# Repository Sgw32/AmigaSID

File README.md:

# AmigaSID - A2000 version is main

Amiga SID Zorro II card

Use at your own risk!!!

Project forked from: 
http://www.amibay.com/showthread.php?108629-Amiga-SID-player-for-Zorro-slot

Player: http://aminet.net/package/misc/emu/FrodoV2_4

Videos:
https://www.youtube.com/watch?app=desktop&v=QOlyukb5uWo
https://www.youtube.com/watch?v=6BfD3O8DvEo

Project information in "original" folder

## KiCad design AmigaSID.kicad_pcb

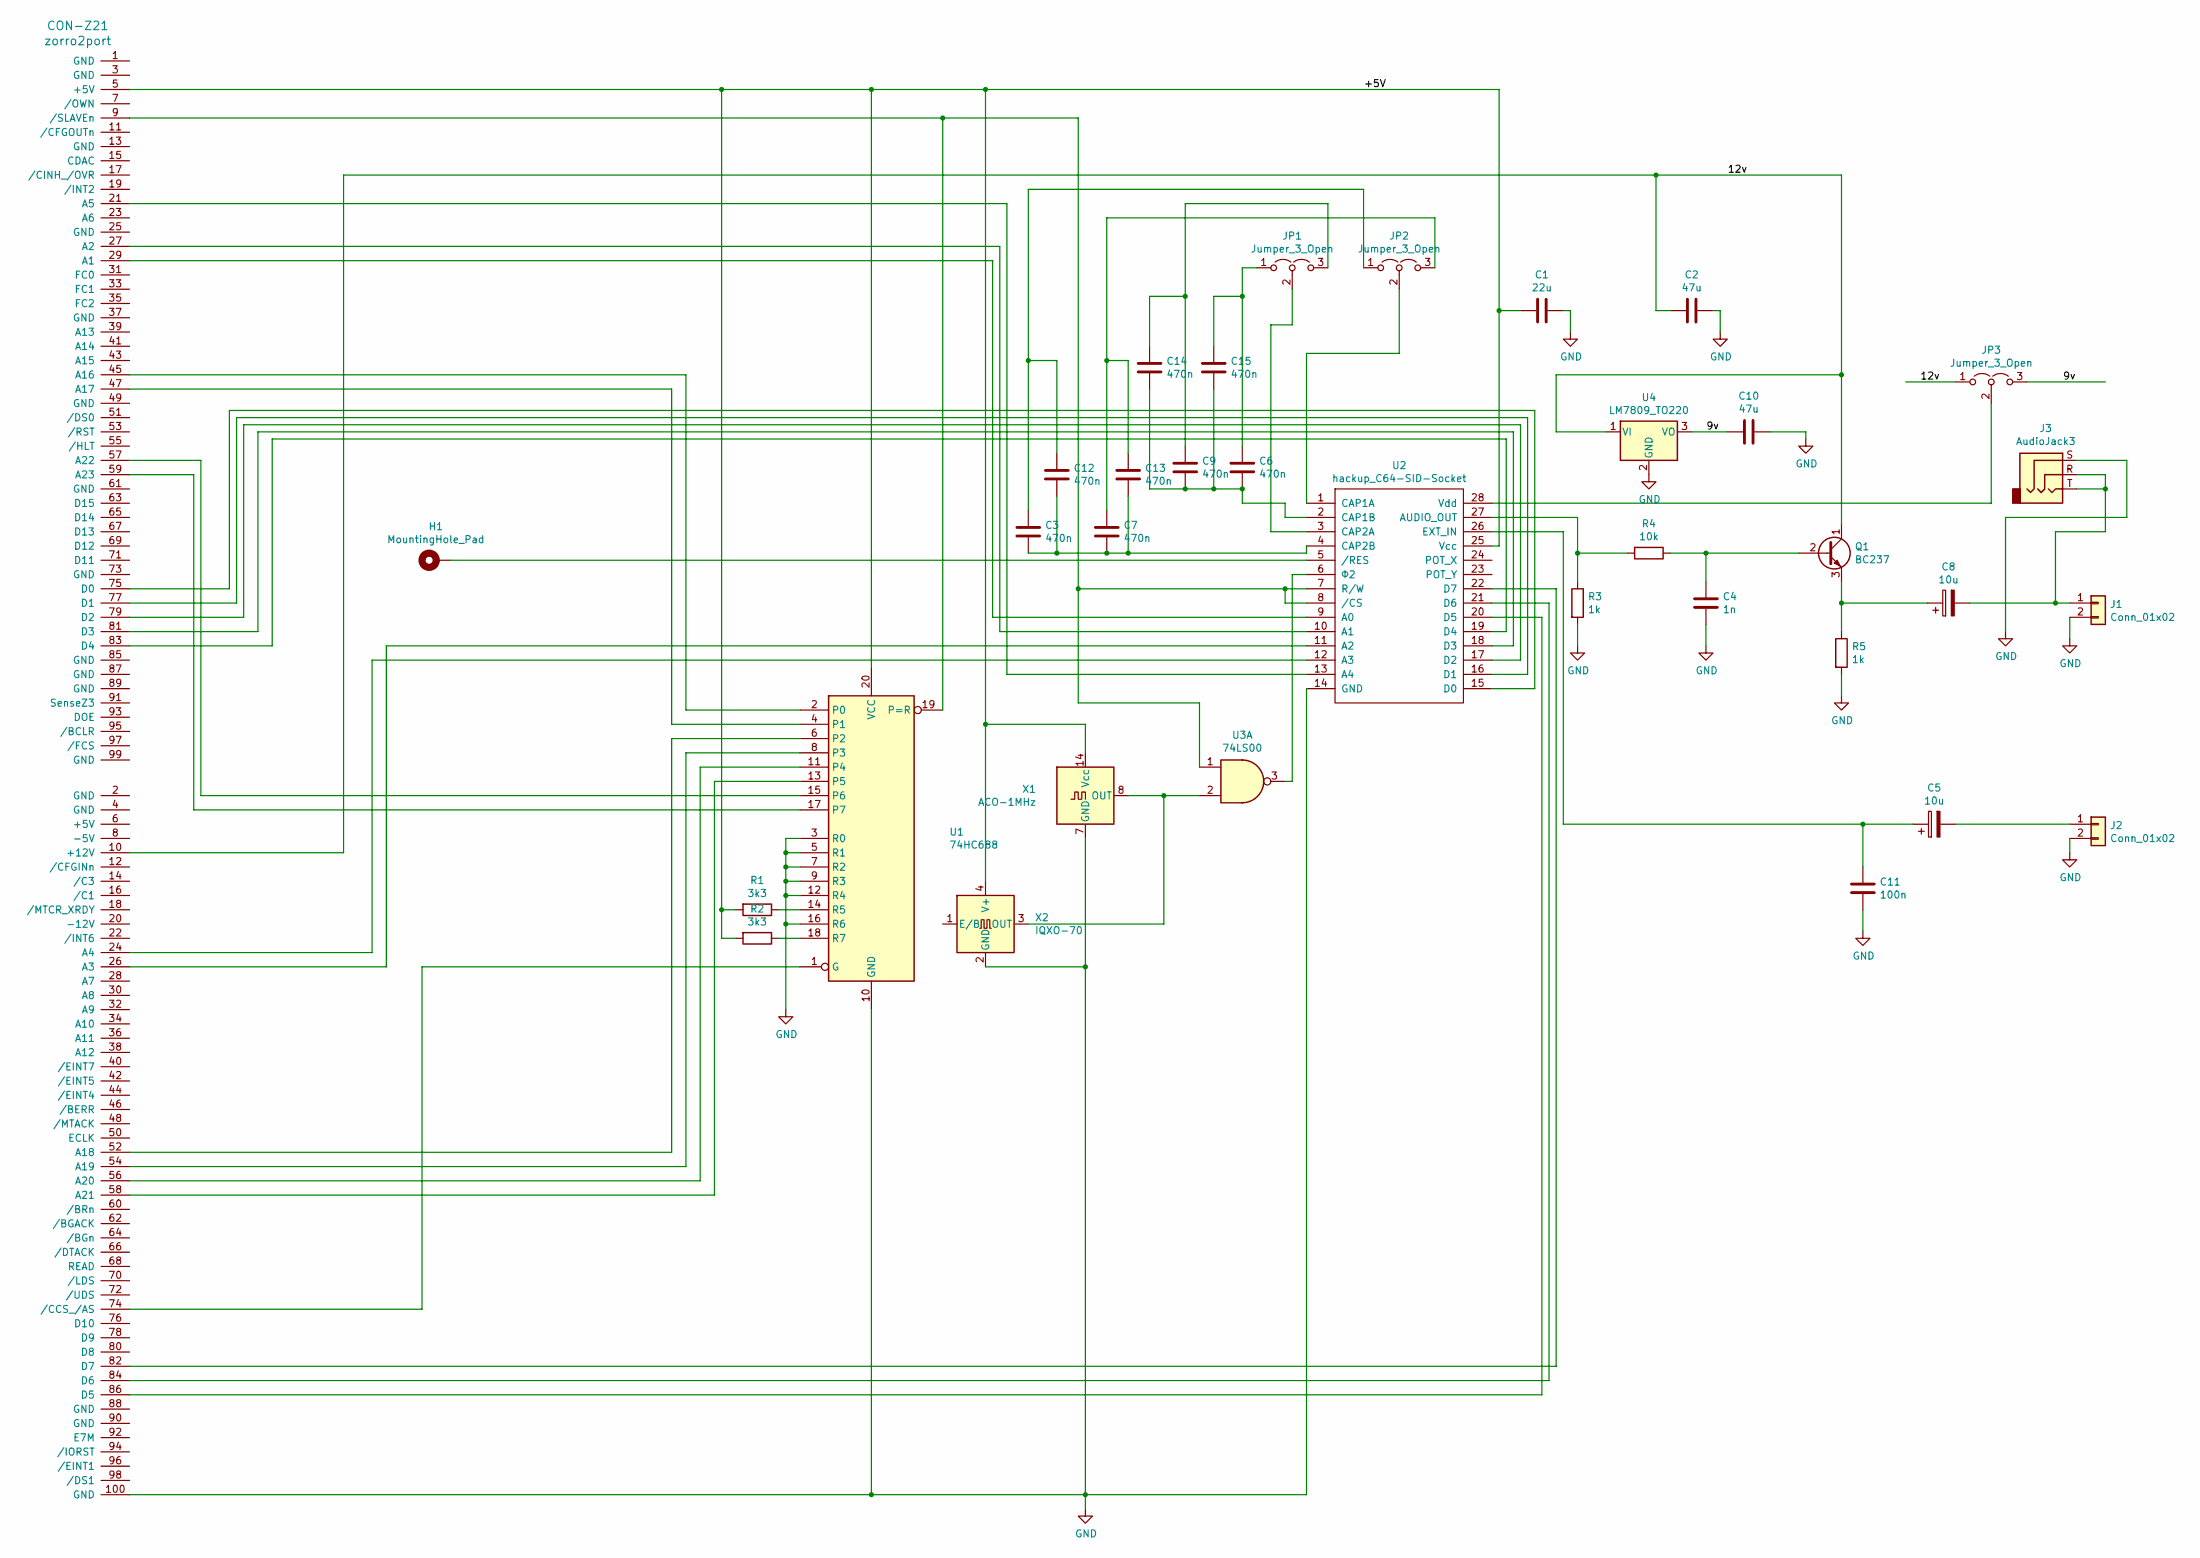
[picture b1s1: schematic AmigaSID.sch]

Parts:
C1: 22u; C_Disc_D4.7mm_W2.5mm_P5.00mm
C2, C10: 47u; C_Disc_D4.7mm_W2.5mm_P5.00mm
C3, C6, C7, C9: 470n; C_Disc_D4.7mm_W2.5mm_P5.00mm
C4: 1n; C_Disc_D4.7mm_W2.5mm_P5.00mm
C5, C8: 10u; CP_Radial_D7.5mm_P2.50mm
C11: 100n; C_Disc_D4.7mm_W2.5mm_P5.00mm
C12, C13, C14, C15: 470n; C_0805_2012Metric
CON-Z21: zorro2port; zorro2card
H1: MountingHole_Pad; Pin_D0.7mm_L6.5mm_W1.8mm_FlatFork
J1, J2: Conn_01x02; TerminalBlock_4Ucon_1x02_P3.50mm_Horizontal
J3: AudioJack3; Jack_3.5mm_CUI_SJ1-3533NG_Horizontal_CircularHoles
JP1, JP2, JP3: Jumper_3_Open; PinHeader_1x03_P2.54mm_Vertical
Q1: BC237; TO-92_Inline
R1, R2: 3k3; R_Axial_DIN0207_L6.3mm_D2.5mm_P10.16mm_Horizontal
R3, R5: 1k; R_Axial_DIN0207_L6.3mm_D2.5mm_P10.16mm_Horizontal
R4: 10k; R_Axial_DIN0207_L6.3mm_D2.5mm_P10.16mm_Horizontal
U1: 74HC688; DIP-20_W7.62mm_Socket_LongPads
U2: hackup_C64-SID-Socket; DIP-28_W15.24mm_Socket_LongPads
U3: 74LS00; DIP-14_W7.62mm_Socket_LongPads
U4: LM7809_TO220; TO-220-3_Vertical
X1: ACO-1MHz; Oscillator_DIP-14
X2: IQXO-70; Oscillator_SMD_IQD_IQXO70-4Pin_7.5x5.0mm

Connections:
/9v: C10.2, JP3.3 (B), U4.3 (VO)
/12v: C2.2, CON-Z21.10 (+12V), JP3.1 (A), Q1.1 (C), U4.1 (VI)
/+5V: C1.2, CON-Z21.5 (+5V), R1.2, R2.2, U1.20 (VCC), U2.25 (Vcc), X1.14 (Vcc), X2.4 (V+)
GND: C1.1, C2.1, C4.2, C10.1, C11.2, CON-Z21.100 (GND), J1.2, J2.2, J3.S, R3.2, R5.2, U1.3 (R0), U1.5 (R1), U1.7 (R2), U1.9 (R3), U1.10 (GND), U1.12 (R4), U1.16 (R6), U2.14 (GND), U4.2 (GND), X1.7 (GND), X2.2 (GND)
unnamed: C4.1, Q1.2 (B), R4.1
unnamed: C5.2, J2.1
unnamed: C8.1, Q1.3 (E), R5.1
unnamed: C8.2, J1.1, J3.R, J3.T
unnamed: C5.1, C11.1, U2.26 (EXT_IN)
unnamed: C3.1, C12.1, JP2.1 (A)
unnamed: C3.2, C7.2, C12.2, C13.2, U2.4 (CAP2B)
unnamed: C7.1, C13.1, JP2.3 (B)
unnamed: C9.1, C14.1, JP1.3 (B)
unnamed: C6.2, C9.2, C14.2, C15.2, U2.2 (CAP1B)
unnamed: C6.1, C15.1, JP1.1 (A)
unnamed: CON-Z21.9 (/SLAVEn), U1.19 (P=R), U2.7 (R/W), U2.8 (/CS), U3.1
unnamed: CON-Z21.21 (A5), U2.13 (A4)
unnamed: CON-Z21.24 (A4), U2.12 (A3)
unnamed: CON-Z21.26 (A3), U2.11 (A2)
unnamed: CON-Z21.27 (A2), U2.10 (A1)
unnamed: CON-Z21.29 (A1), U2.9 (A0)
unnamed: CON-Z21.45 (A16), U1.2 (P0)
unnamed: CON-Z21.47 (A17), U1.4 (P1)
unnamed: CON-Z21.52 (A18), U1.6 (P2)
unnamed: CON-Z21.54 (A19), U1.8 (P3)
unnamed: CON-Z21.56 (A20), U1.11 (P4)
unnamed: CON-Z21.57 (A22), U1.15 (P6)
unnamed: CON-Z21.58 (A21), U1.13 (P5)
unnamed: CON-Z21.59 (A23), U1.17 (P7)
unnamed: CON-Z21.74 (/CCS_/AS), U1.1 (G)
unnamed: CON-Z21.75 (D0), U2.15 (D0)
unnamed: CON-Z21.77 (D1), U2.16 (D1)
unnamed: CON-Z21.79 (D2), U2.17 (D2)
unnamed: CON-Z21.81 (D3), U2.18 (D3)
unnamed: CON-Z21.82 (D7), U2.22 (D7)
unnamed: CON-Z21.83 (D4), U2.19 (D4)
unnamed: CON-Z21.84 (D6), U2.21 (D6)
unnamed: CON-Z21.86 (D5), U2.20 (D5)
unnamed: H1.1, U2.5 (/RES)
unnamed: JP1.2 (C), U2.3 (CAP2A)
unnamed: JP2.2 (C), U2.1 (CAP1A)
unnamed: JP3.2 (C), U2.28 (Vdd)
unnamed: R1.1, U1.14 (R5)
unnamed: R2.1, U1.18 (R7)
unnamed: R3.1, R4.2, U2.27 (AUDIO_OUT)
unnamed: U2.6 (Φ2), U3.3
unnamed: U3.2, X1.8 (OUT), X2.3 (OUT)

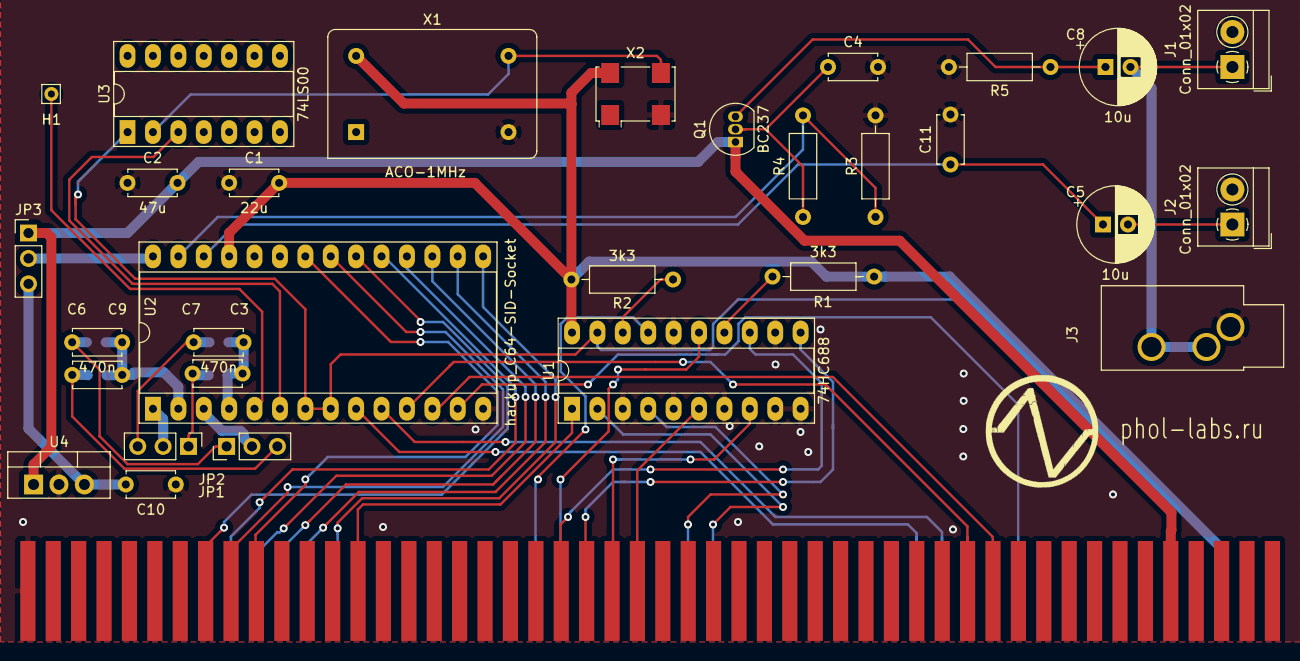
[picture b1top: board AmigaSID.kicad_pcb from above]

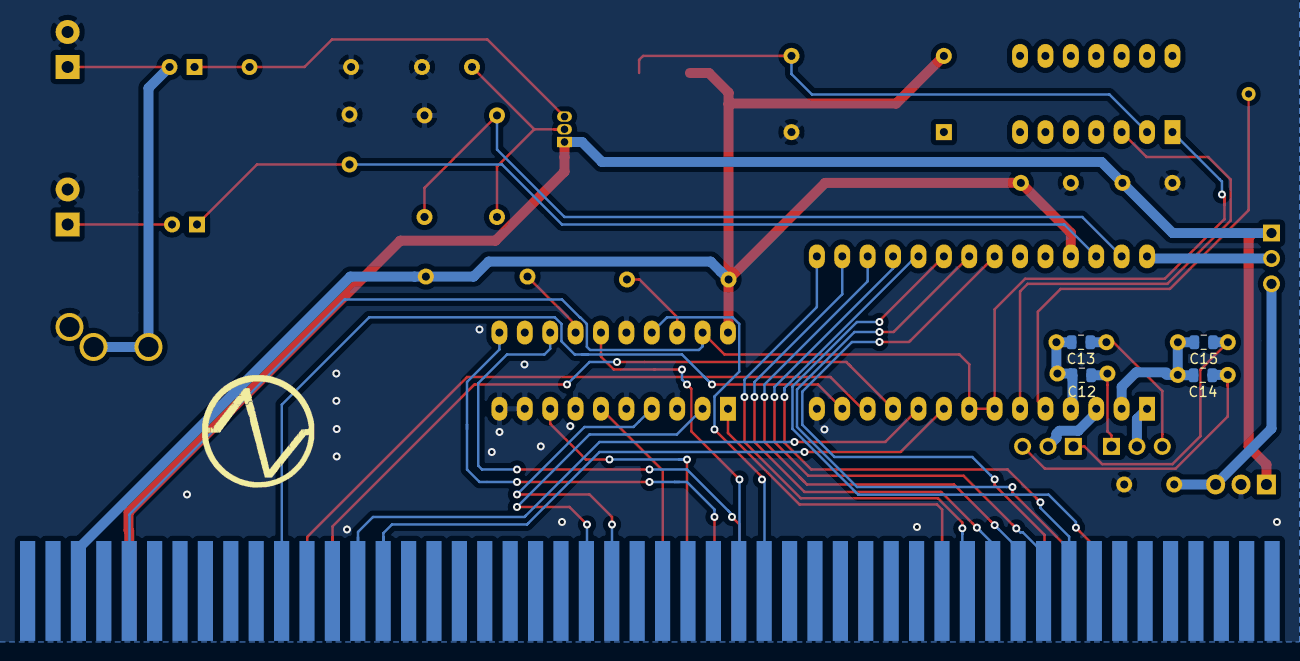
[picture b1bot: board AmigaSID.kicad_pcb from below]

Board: 2 copper layers, 35 parts (4 on the bottom side), 47 nets.
